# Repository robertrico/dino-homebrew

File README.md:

# DINO

**D**iscrete **I**ntegrated **N**ISC **O**perator — an 8-bit CPU built from
74-series logic. No microcontroller, no FPGA, no CPU chip: every register,
every bus, every gate is a chip you can put a probe on.

Schematics in KiCad, horizontal microcode in three EEPROMs, a ROM monitor
over a 16550 serial card, and SCELBAL BASIC running on it.

<table>
<tr>
<td width="50%"></td>
<td width="50%"></td>
</tr>
<tr>
<td><b>The prototype</b> (2026-09-10). Every module on breadboards, wired
by hand, running at 1.024 MHz.</td>
<td><b>Rev 1.0</b> (2026-10-29). The same netlist on one 4-layer board,
299 x 270 mm, eight card slots. Through fab review.</td>
</tr>
</table>

## Status, 2026-10-29

**The breadboard machine is complete.** It runs at 1.024 MHz off its own
crystal, executes from ROM and RAM, takes interrupts, and talks over serial.

- **174-instruction ISA.** `PROG_isa` passes 147 subtests; `PROG_isasoak`
  ran 50 consecutive passes (470,400 subtest executions) clean.
- **Stack, CALL/RET, execute-from-RAM.** All 32K of RAM (0x8000-0xFFFF)
  holds data and fetches instructions.
- **Memory-mapped I/O.** A 16K I/O window with eight 2K card slots: a DIP
  switch card and a PC16550D serial card at 9600 8N1.
- **ROM monitor.** `D`ump, `W`rite, `O`ut, `L`oad hex, `G`o (a CALL, so a
  RET comes back to the prompt).
- **Interrupts.** One vector, `0x9090` in RAM; the interrupt monitor takes
  serial input on the 16550's receive interrupt and breaks on Ctrl-C.
- **Add-with-carry.** `ADC`/`SBB`/`ACI`/`SBI` through one '157 on the ALU's
  carry-in.
- **SCELBAL BASIC** (the 1974 8008 BASIC), machine-translated into DINO
  assembly, runs out of ROM: `PRINT 2/3` gives ` 0.6666667`.

**Rev 1.0, the PCB.** Five boards ordered from PCBWay (2026-10-30).
4 layers (GND and +5V planes inside), KiCad DRC 0 unconnected / 0 errors,
schematic parity 0. Routed by Freerouting 2.5.0. Added for bring-up: a clock
select header (1.024 MHz, 512k, 256k, 128k, or a debounced single-step
button), a 16-signal logic analyzer header, 15 scope ground loops, and
unpopulated cap pads on the clock nets. Power is an ATX supply into the
24-pin header.

**Next:** bring Rev 1.0 up, move the serial card onto an edge card, then
CompactFlash and a floppy card. DINO will not get DMA; that goes to the
next machine.

---

## The machine

**8-bit data, 16-bit address.** Horizontal microcode, no pipeline. A
**24-bit control word** per T-state comes out of three AT28C64B EEPROMs
(`U9`, `U15`, `U23`) addressed by `{opcode, T-state}`. T0 is the fetch row
for every opcode; a '163 T-counter steps the rows until `END`.

The source, destination and misc fields are each a 3-bit '138 decode, with
bank-select bits for a second bank, so **two bus sources can never be on at
once**: mutual exclusion is the decoder, not the microcode's good behaviour.

**Memory map:**

```
0x0000-0x3FFF   ROM (U24, 28C256, 16K decoded)
0x4000-0x7FFF   I/O window, eight 2K card slots
                  0x4000 card 0  DIP switches
                  0x4800 card 1  PC16550D serial, 9600 8N1
0x8000-0xFFFF   RAM, 32K
```

**ALU:** two 74F382s, ripple carry. All four flags latch in a '273 and only
update when the ALU is the source.

**Commit discipline:** everything that changes state is clock-qualified and
commits while the clock is low — register loads through `NOR(~LOAD, CLK)`,
the RAM write through `NAND(WRITE_DIR, WR_GATE)`, PC load, clear and count
each gated on their own. Bus output enables are ungated, so a decode runt
lands while CLK is high and reaches nothing. The one exception was the fetch
row, where the instruction register is transparent during CLK low; the RAM
write is gated off in T-state 0 to close it. The machine is fully static, so
the clock can stop.

**HALT is `0xFF`**, so an erased EEPROM halts instead of running wild.

**Adding an instruction costs a three-ROM burn.** Image CRCs are pinned as
literals in `test_microcode_gen.py`, so a reburn is always deliberate.

---

## The part worth reading about

Building a CPU from discrete logic is a known exercise. The interesting
problem is different: **on a breadboard, with 80+ chips and a thousand
jumpers, how do you know the machine you built is the machine you drew?**

```
schematic  ──▶  netlist audit  ──▶  generated artifacts  ──▶  bench
 (KiCad)        (gate equations      (microcode, ROMs,        (coverage ROMs:
                 extracted, not       slot maps, landing       each one names
                 eyeballed)           lists, answer keys)      its expected byte)
```

The rule underneath it: **nothing is retyped.** Every table in this repo —
the microcode, the program ROMs, the breadboard slot maps, the wiring
landing lists, the card-edge pinout — is generated by a script with its own
host tests, most of them from the KiCad netlist. A hand-maintained table
drifts the moment someone moves a wire, and drift is invisible until it
costs you an evening.

Every test assertion is **netlist-verified before it is written**. Reading
a schematic and typing what you think a gate does is how you write a test
that agrees with your misunderstanding.

The answer key is `simulate()` in `progrom_gen.py`: it interprets the real
microcode rows and computes what the output LEDs should read for each
coverage image. Each image ends in `HALT` with one byte on the LEDs, and the
byte either matches or it names what broke.

### Rules that were paid for on the bench

Each of these exists because something went wrong first:

- **Rails first.** A random, probe-sensitive fault that doesn't care which
  program runs is not in the datapath. Measure ground and VCC on every board
  before building a logic model. One halt hunt (2026-09-01) was 460 mV of
  ground offset.
- **Mirror-witness.** A write-then-read through the same bus bank is
  permutation-blind — a flipped jumper bank cancels itself out. Every
  module needs at least one asymmetric path.
- **A witness that rewrites the same value sees nothing.** Every plant must
  differ from what the cell already held.
- **Rate is not data.** Halt rates moved from 7/8 to 1/22 with probes, a cap
  and warmth. Use a witness that cannot miss: a pulse trigger, a planted
  byte, a soak with a count.
- **A change that is logically identical and only faster is a timing
  change**, and the simulator is blind to it.
- **No blind counters.** A failing assertion must name the lying signal, or
  the test is just a rumour.

### Faults this method caught

| Fault | How it was found |
|---|---|
| `U18.1` (OE) on `MDR_OUT` instead of `~MDR_OUT` | enable polarity inverted; cascaded into four failing tests until bus-fight analysis fingered it |
| PORTF→MDR jumper bank reversed | invisible to every A/B/C round trip, caught only by the asymmetric OUT-register path |
| `MDR5`↔`MDR6` crossed | decoded from byte 0 arithmetic alone: `0xA5 → 0xC5` is exactly a bit-5/6 exchange |
| Bridge DIR/EN keyed on destination instead of source | schematic bug — ADD could never have committed. Found by netlist audit before the board existed |
| `A8`-`A11` address rotation on the microcode ROM | the address-order test named every rotated line |
| A RET fetched from RAM latching `0xFF` | a 14 ns `~WE` runt during the fetch row; caught on a pulse trigger, fixed by gating the write off in T-state 0 |
| The ALU latching half its next answer | its latch enable on raw CLK at the end of a stub sat at 1.0-1.2 V for 20 ns; now driven by a gate |

---

## Layout

```
dino_v0_0_2/     KiCad project: the mainboard schematics and the Rev 1.0 PCB
dino_bus/        card-edge connector symbol and socket footprint
dino_io/         card 0, the DIP switch card
dino_serial/     card 1, the 16550 serial card
asm/             program sources (.asm); asm/ram/ loads over serial
roms/            the burned images, CRCs and expected outputs (roms/README.md)
docs/notes/      generators, design notes, host tests
docs/captures/   scope, logic analyzer and PCB review captures
datasheets/      74-series and memory parts
```

| Script (`docs/notes/`) | Emits |
|---|---|
| `kicad_netlist.py` | `build_report()` — the netlist oracle everything else asks |
| `kicad_contracts.py` | per-sheet contracts, `--continuity` landing lists, `--since` change lists |
| `microcode_gen.py` | the three microcode images, CRCs, header |
| `progrom_gen.py` | program ROMs and the `simulate()` answer key |
| `isatest_gen.py` | the ISA self-test family (`isa`, `isasoak`, ...) |
| `roms_readme_gen.py` | `roms/README.md` — the inventory read at the burner |
| `layout_gen.py` | breadboard placement, slot maps, wiring guides |
| `bus_gen.py` | the card-edge pinout, symbol and footprint |
| `netsim_gen.py` | the twin: the Rev 1.0 netlist as gate-level Verilog (`netsim/`) |
| `netsim_suite.py` | every runnable image on the twin against the oracle (`make twin`) |

```bash
make test               # host tests
make expected           # every coverage image's expected output
make assemble-<name>    # asm/<name>.asm -> roms/PROG_<name>.bin
make load-<name>        # asm/ram/<name>.asm over serial into RAM
make monitor            # minicom on the serial card
```

Burning is done by hand on a TL866; the tools verify, they never program.

---

## Retired

**The ATmega2560 bring-up rig** brought the machine up one module at a
time, then one integration block at a time, shedding wires as each block
was proven. Retired 2026-08-24. `tests/dino_bringup/` stays for its ROM
burn targets.

**The FPGA twin** generated VHDL from an earlier netlist. It was perfect
logic, so it could not see the faults that mattered, which were build,
analog and glitch faults. Retired 2026-08-24 and deleted 2026-10-30. The
only twin now is `netsim/`: the Rev 1.0 netlist exactly as drawn, chip by
chip and pin by pin, simulated in Icarus with typical delays. `make twin`
runs every image that needs no card (43 of them, `isa` and `isasoak`
included) and all match the oracle. The breadboard had a fetch glitch that the T0 write
gate fixed; unmeasured on the PCB; the twin is logically identical, gate
included.

---

*Schematic PDF: [`dino_v0_0_2/dino_v0_0_2.pdf`](dino_v0_0_2/dino_v0_0_2.pdf)*

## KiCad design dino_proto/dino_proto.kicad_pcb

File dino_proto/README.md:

# dino_proto — the DINO prototype slot card

A perfboard with the bus edge and the slot decode every DINO card
repeats. Plug it into any of J1-J8 on the Rev 1.0 mainboard, pick the
slot with one shunt, bodge the card on the grid. Generated by
`docs/notes/proto_card_gen.py` from `bus_gen.BUS`; proved by
`docs/notes/test_proto_card.py`. Design and history: `.git/sdd/PROTO_CARD.md`.

    python3 docs/notes/proto_card_gen.py --write      # the project, unrouted
    python3 docs/notes/proto_card_gen.py --route 200  # Freerouting the band, DRC after

191.8 x 70 mm, 2-layer, all through-hole. The finger tab (65.8 mm) is
near the right end: the body runs 18 mm past the tab's right end (the
mainboard's edge is a future case wall; the cap is 20) and 108 mm to the
left, over the mainboard.

## What is on it

| Ref | Part | Does |
|-----|------|------|
| J1  | 2x25 fingers | the bus, pin n opposite pin n+25 (`PERIPHERAL_BUS.md` section 1) |
| J2  | 2x25 pin header | the edge repeated 1:1, pin n = edge pin n, numbered BY ROWS (1-25 front row, nearest the fingers; 26-50 back row) for a 50-way IDC ribbon to a breadboard. Silk: one label per column, "front/back", read as a picture of the column: the word at the top of the label is the top (back) hole, the word at the bottom the bottom (front) hole; "F/B" at pin 1; SPnn = spare, 3V3 = +3.3V |
| U1  | 74LS138 | slot decode: A0-A2 = M11-M13, E1 = `~{IO_SEL}`, E2 = GND, E3 = +5V, as the serial card's U101 |
| JP1 | 2x8 header | slot select, ONE shunt |
| U2  | 74LS32 | `~{CARD_RD}` = `~{CARD_SEL}` or `~{IO_RD_Q}`; `~{CARD_WR}` = `~{CARD_SEL}` or `~{IO_WR}`; two gates spare |
| J3  | 2x6 header | the decoded signals for the bodge |
| J4  | 1x4 header | the spare '32 gates |
| R1  | 4.7k | `~{CARD_SEL}` pull-up (no shunt = no window) |
| R2, R3 | 4.7k | park the spare gates (A high); leave one out to use its gate, see J4 |
| C1, C2 | 100 nF | U1, U2 decoupling |
| C3  | 10 uF | +5V bulk at the edge |

## JP1 — slot select

Top row `O0`..`O7` (the '138's outputs, left to right, silk 0-7); bottom
row all `~{CARD_SEL}`. One shunt in column n puts the card in slot n:

| slot | window        | slot | window        |
|------|---------------|------|---------------|
| 0    | 0x4000-0x47FF | 4    | 0x6000-0x67FF |
| 1    | 0x4800-0x4FFF | 5    | 0x6800-0x6FFF |
| 2    | 0x5000-0x57FF | 6    | 0x7000-0x77FF |
| 3    | 0x5800-0x5FFF | 7    | 0x7800-0x7FFF |

Two shunts short two '138 outputs together: never. Slot 0 is card zero
(the DIP switch), slot 1 the serial card, on the breadboard machine.

## J3 — the card's signals

| pin | signal          | pin | signal |
|-----|-----------------|-----|--------|
| 1   | `~{CARD_SEL}`   | 7   | `O3`   |
| 2   | `~{CARD_RD}`    | 8   | `O4`   |
| 3   | `~{CARD_WR}`    | 9   | `O5`   |
| 4   | `O0`            | 10  | `O6`   |
| 5   | `O1`            | 11  | `O7`   |
| 6   | `O2`            | 12  | GND    |

`O0`-`O7` are the raw decoder outputs, for a bodge that wants a second
window. The rule for every card (PHASE_G): drive W only while
`~{CARD_RD}` is low, take data on `~{CARD_WR}`; nothing else goes back
on the bus (CARD-2).

## J4 — the spare '32 gates

| pin | signal | gate |
|-----|--------|------|
| 1   | 3B     | gate 3 input; 3A pulled up by R2 |
| 2   | 3Y     | gate 3 output |
| 3   | 4B     | gate 4 input; 4A pulled up by R3 |
| 4   | 4Y     | gate 4 output |

With A pulled high an OR gate's output is high whatever B does. To use
a spare gate as a 2-input OR, leave its pull-up out (R2 for gate 3, R3
for gate 4) and wire A at the empty resistor's pad: the one on the U2
side is U2 pin 9 (3A) / pin 12 (4A). With the pull-up fitted the gate
is parked.

## The grid

0.1 in plated holes, drill 1.0 mm, pad 1.8 mm, both sides, every hole
on its own. Rows top to bottom: +12, -12, 3V3 (square holes, one row
each), then +5V / A-E / GND, +5V / F-J / GND, +5V / K-M. A rail row is a
row of SQUARE holes joined by a masked trace (GND 1.5 mm, +5V 1.2 mm,
bias 0.6 mm, both layers); the round holes beside it are free. A 0.3 in
DIP sits on a band's rows 1 and 4 with VCC and GND one row away.
Columns 1-71 numbered every fifth on the top edge, rows lettered on the
right. No track of the card's own copper runs through the grid (rule
areas, DRC-checked).

The band's own +5V and GND rails are hole-less traces just above the
chips, fed from the grid's rows down the left margin. The six J2-to-band
signals (M11-M13, `~{IO_SEL}`, `~{IO_RD_Q}`, `~{IO_WR}`) run as lanes
between the grid and the band.

## Rails on the edge

+5V, GND, +12V, -12V, +3.3V are what the ATX unit delivers (POWER.md
section 8). -12V is 50-100 mA for the whole machine. This card draws
nothing from +12V/-12V/+3.3V itself; a bodge that does declares it.

## Fab

PCBWay 2-layer, 1.6 mm, gold fingers with a bevel. Open before the
first order: the Sullins EBC25DCWN slot opening against the 65.8 mm tab
(no catalog on disk; `PERIPHERAL_BUS.md` OPEN 2).

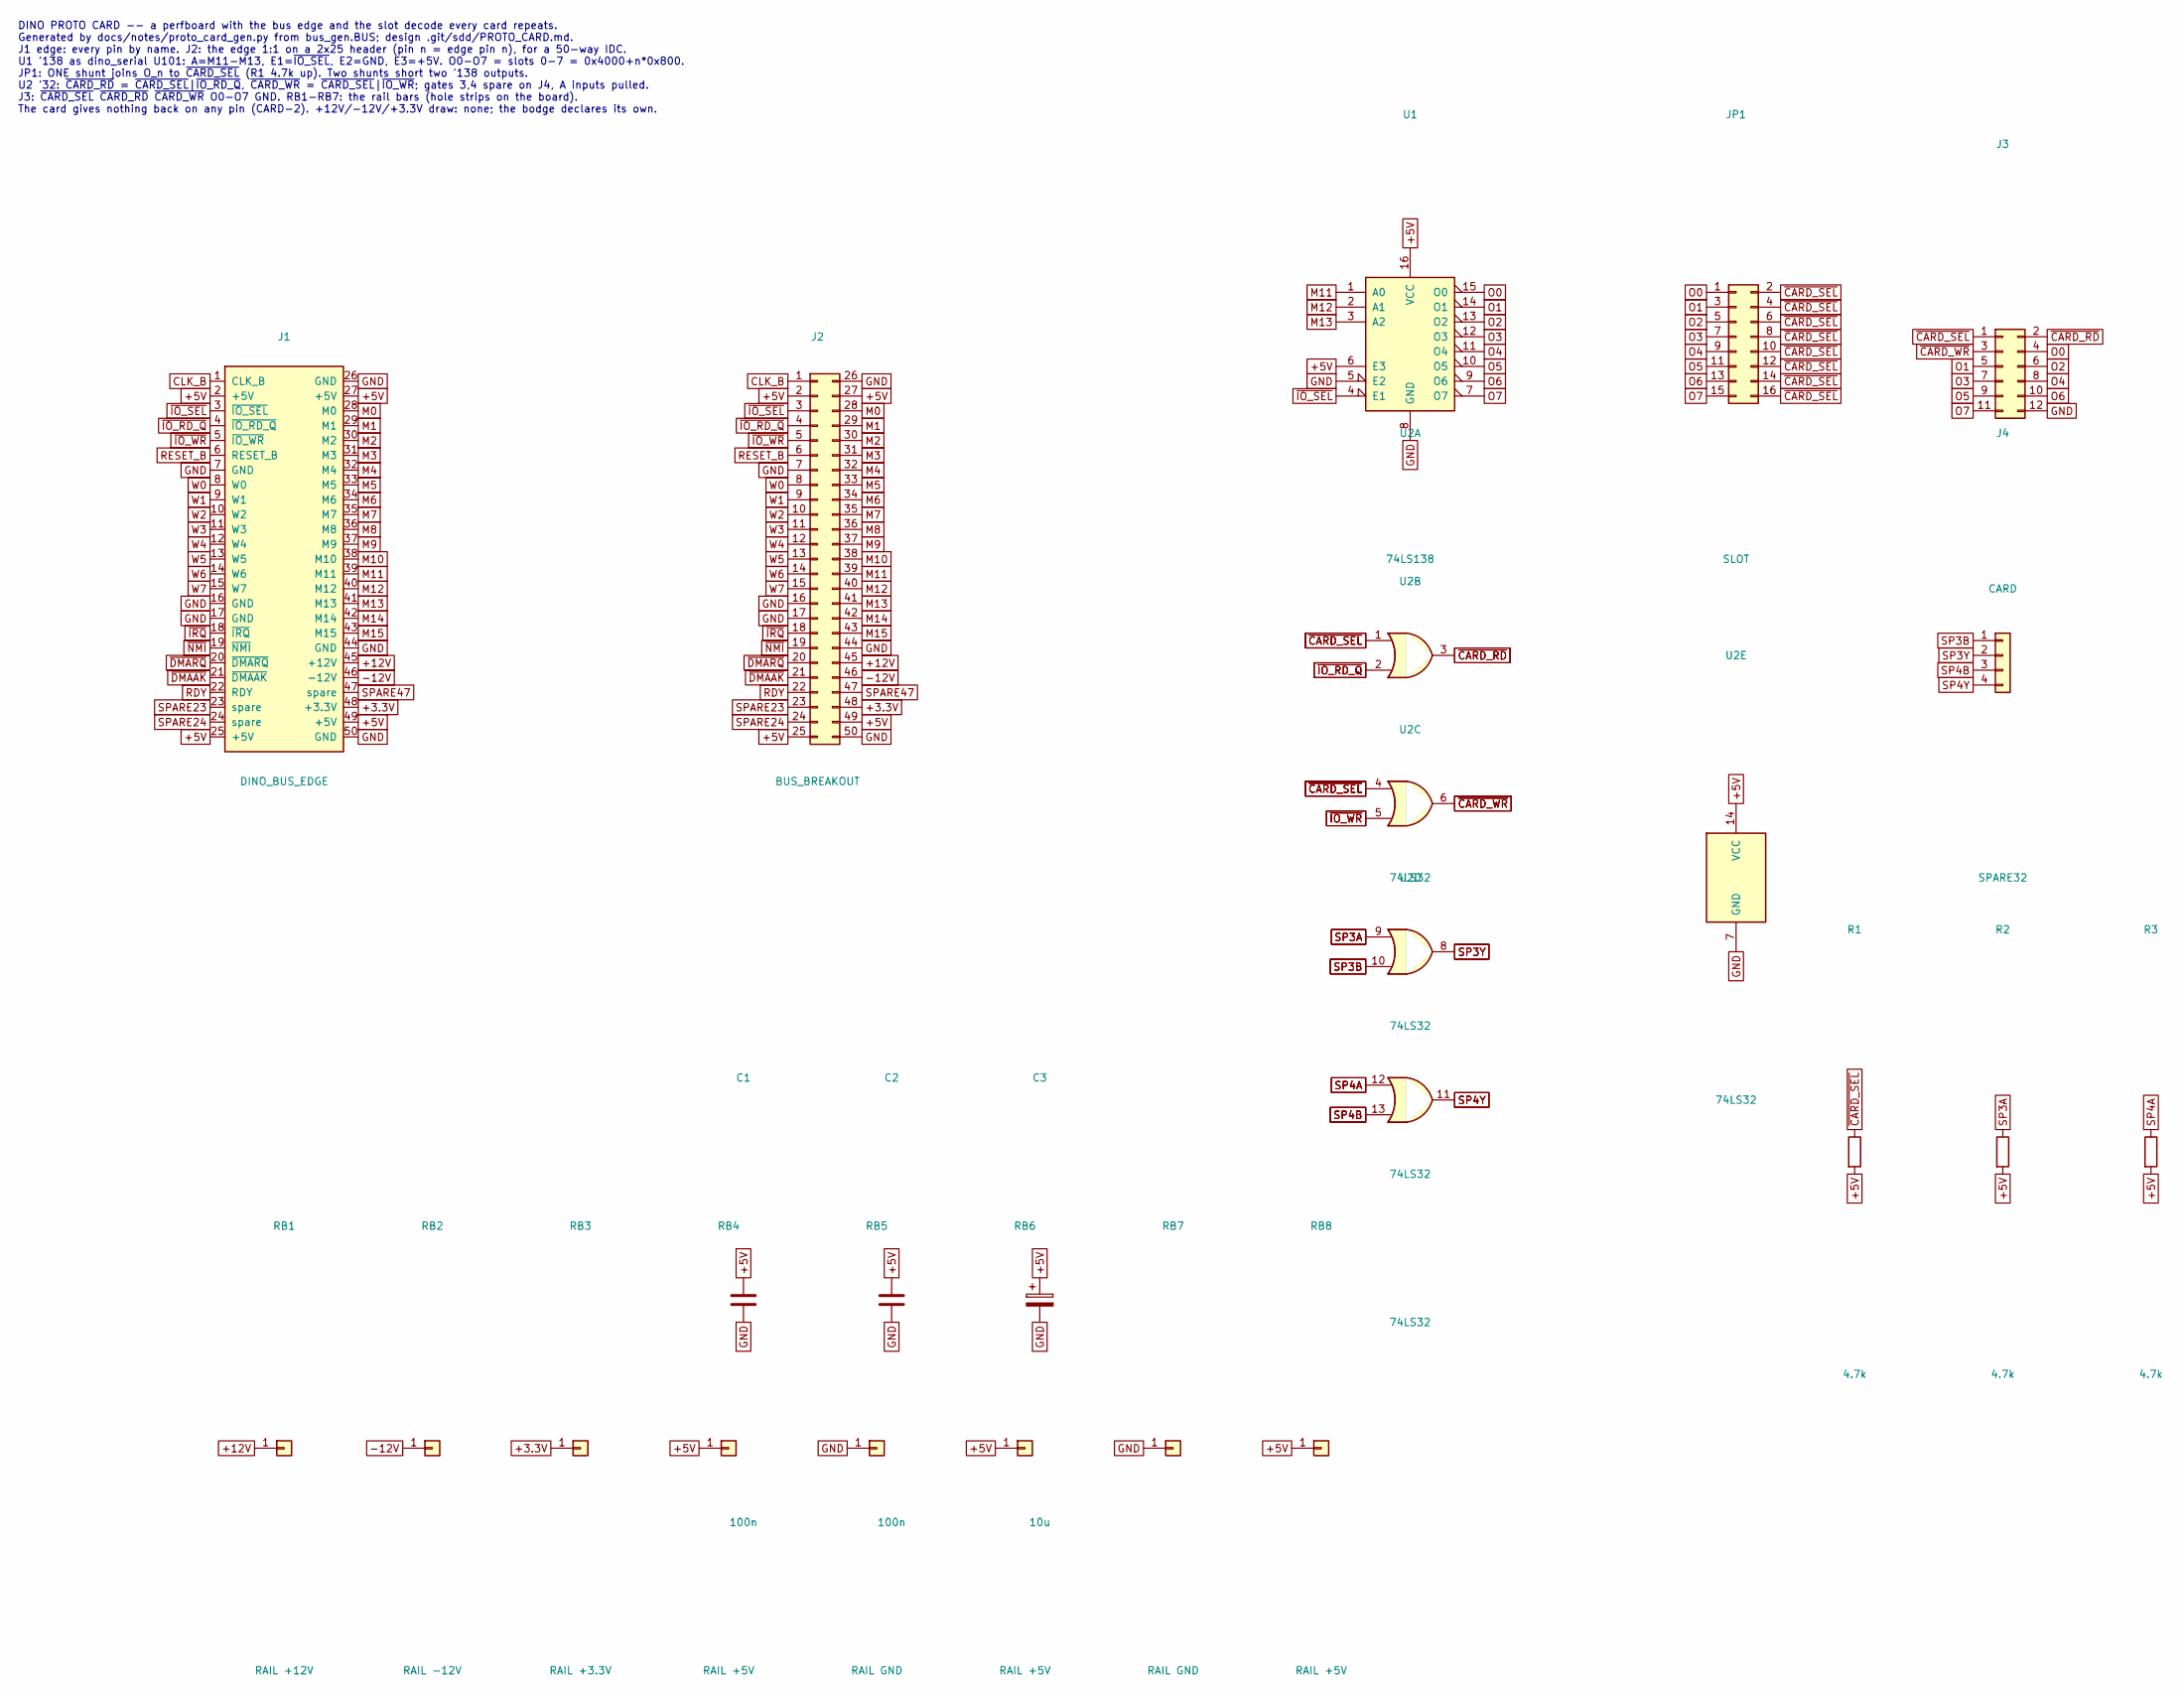
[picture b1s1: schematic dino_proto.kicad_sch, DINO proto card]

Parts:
C1, C2: 100n; C_Disc_D5.0mm_W2.5mm_P5.00mm
C3: 10u; CP_Radial_D5.0mm_P2.50mm
J1: DINO_BUS_EDGE; EdgeFingers_2x25_P2.54mm
J2: BUS_BREAKOUT; PinHeader_2x25_Rows_P2.54mm
J3: CARD; PinHeader_2x06_P2.54mm_Vertical
J4: SPARE32; PinHeader_1x04_P2.54mm_Vertical
JP1: SLOT; PinHeader_2x08_P2.54mm_Vertical
R1, R2, R3: 4.7k; R_Axial_DIN0207_L6.3mm_D2.5mm_P7.62mm_Horizontal
RB1: RAIL +12V; RailHoles_1x71_P2.54mm
RB2: RAIL -12V; RailHoles_1x71_P2.54mm
RB3: RAIL +3.3V; RailHoles_1x71_P2.54mm
RB4, RB6, RB8: RAIL +5V; RailHoles_1x71_P2.54mm
RB5, RB7: RAIL GND; RailHoles_1x71_P2.54mm
U1: 74LS138; DIP-16_W7.62mm_Socket
U2: 74LS32; DIP-14_W7.62mm_Socket

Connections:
+3.3V: J1.48 (+3.3V), J2.48, RB3.1
+5V: C1.1, C2.1, C3.1, J1.2 (+5V), J1.25 (+5V), J1.27 (+5V), J1.49 (+5V), J2.2, J2.25, J2.27, J2.49, R1.2, R2.2, R3.2, RB4.1, RB6.1, RB8.1, U1.6 (E3), U1.16 (VCC), U2.14 (VCC)
+12V: J1.45 (+12V), J2.45, RB1.1
-12V: J1.46 (-12V), J2.46, RB2.1
CLK_B: J1.1 (CLK_B), J2.1
GND: C1.2, C2.2, C3.2, J1.7 (GND), J1.16 (GND), J1.17 (GND), J1.26 (GND), J1.44 (GND), J1.50 (GND), J2.7, J2.16, J2.17, J2.26, J2.44, J2.50, J3.12, RB5.1, RB7.1, U1.5 (E2), U1.8 (GND), U2.7 (GND)
M0: J1.28 (M0), J2.28
M1: J1.29 (M1), J2.29
M2: J1.30 (M2), J2.30
M3: J1.31 (M3), J2.31
M4: J1.32 (M4), J2.32
M5: J1.33 (M5), J2.33
M6: J1.34 (M6), J2.34
M7: J1.35 (M7), J2.35
M8: J1.36 (M8), J2.36
M9: J1.37 (M9), J2.37
M10: J1.38 (M10), J2.38
M11: J1.39 (M11), J2.39, U1.1 (A0)
M12: J1.40 (M12), J2.40, U1.2 (A1)
M13: J1.41 (M13), J2.41, U1.3 (A2)
M14: J1.42 (M14), J2.42
M15: J1.43 (M15), J2.43
O0: J3.4, JP1.1, U1.15 (O0)
O1: J3.5, JP1.3, U1.14 (O1)
O2: J3.6, JP1.5, U1.13 (O2)
O3: J3.7, JP1.7, U1.12 (O3)
O4: J3.8, JP1.9, U1.11 (O4)
O5: J3.9, JP1.11, U1.10 (O5)
O6: J3.10, JP1.13, U1.9 (O6)
O7: J3.11, JP1.15, U1.7 (O7)
RDY: J1.22 (RDY), J2.22
RESET_B: J1.6 (RESET_B), J2.6
SP3A: R2.1, U2.9
SP3B: J4.1, U2.10
SP3Y: J4.2, U2.8
SP4A: R3.1, U2.12
SP4B: J4.3, U2.13
SP4Y: J4.4, U2.11
SPARE23: J1.23 (spare), J2.23
SPARE24: J1.24 (spare), J2.24
SPARE47: J1.47 (spare), J2.47
W0: J1.8 (W0), J2.8
W1: J1.9 (W1), J2.9
W2: J1.10 (W2), J2.10
W3: J1.11 (W3), J2.11
W4: J1.12 (W4), J2.12
W5: J1.13 (W5), J2.13
W6: J1.14 (W6), J2.14
W7: J1.15 (W7), J2.15
~CARD_RD: J3.2, U2.3
~CARD_SEL: J3.1, JP1.2, JP1.4, JP1.6, JP1.8, JP1.10, JP1.12, JP1.14, JP1.16, R1.1, U2.1, U2.4
~CARD_WR: J3.3, U2.6
~DMAAK: J1.21 (~DMAAK), J2.21
~DMARQ: J1.20 (~DMARQ), J2.20
~IO_RD_Q: J1.4 (~IO_RD_Q), J2.4, U2.2
~IO_SEL: J1.3 (~IO_SEL), J2.3, U1.4 (E1)
~IO_WR: J1.5 (~IO_WR), J2.5, U2.5
~IRQ: J1.18 (~IRQ), J2.18
~NMI: J1.19 (~NMI), J2.19

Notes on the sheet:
DINO PROTO CARD -- a perfboard with the bus edge and the slot decode every card repeats. Generated by docs/notes/proto_card_gen.py from bus_gen.BUS; design .git/sdd/PROTO_CARD.md. J1 edge: every pin by name. J2: the edge 1:1 on a 2x25 header (pin n = edge pin n), for a 50-way IDC. U1 '138 as dino_s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

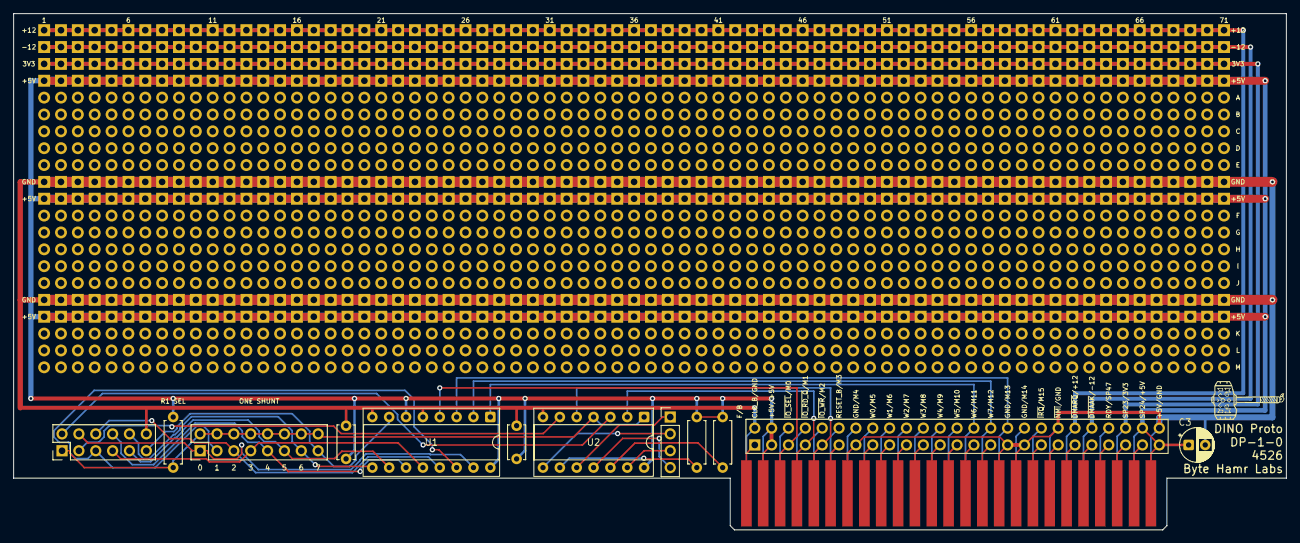
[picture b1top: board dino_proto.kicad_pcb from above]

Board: 2 copper layers, 191.8 x 77.8 mm, 23 parts (0 on the bottom side), 59 nets.

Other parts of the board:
G1: ProtoGrid_923_P2.54mm
LOGO1: hamr_logo_xs

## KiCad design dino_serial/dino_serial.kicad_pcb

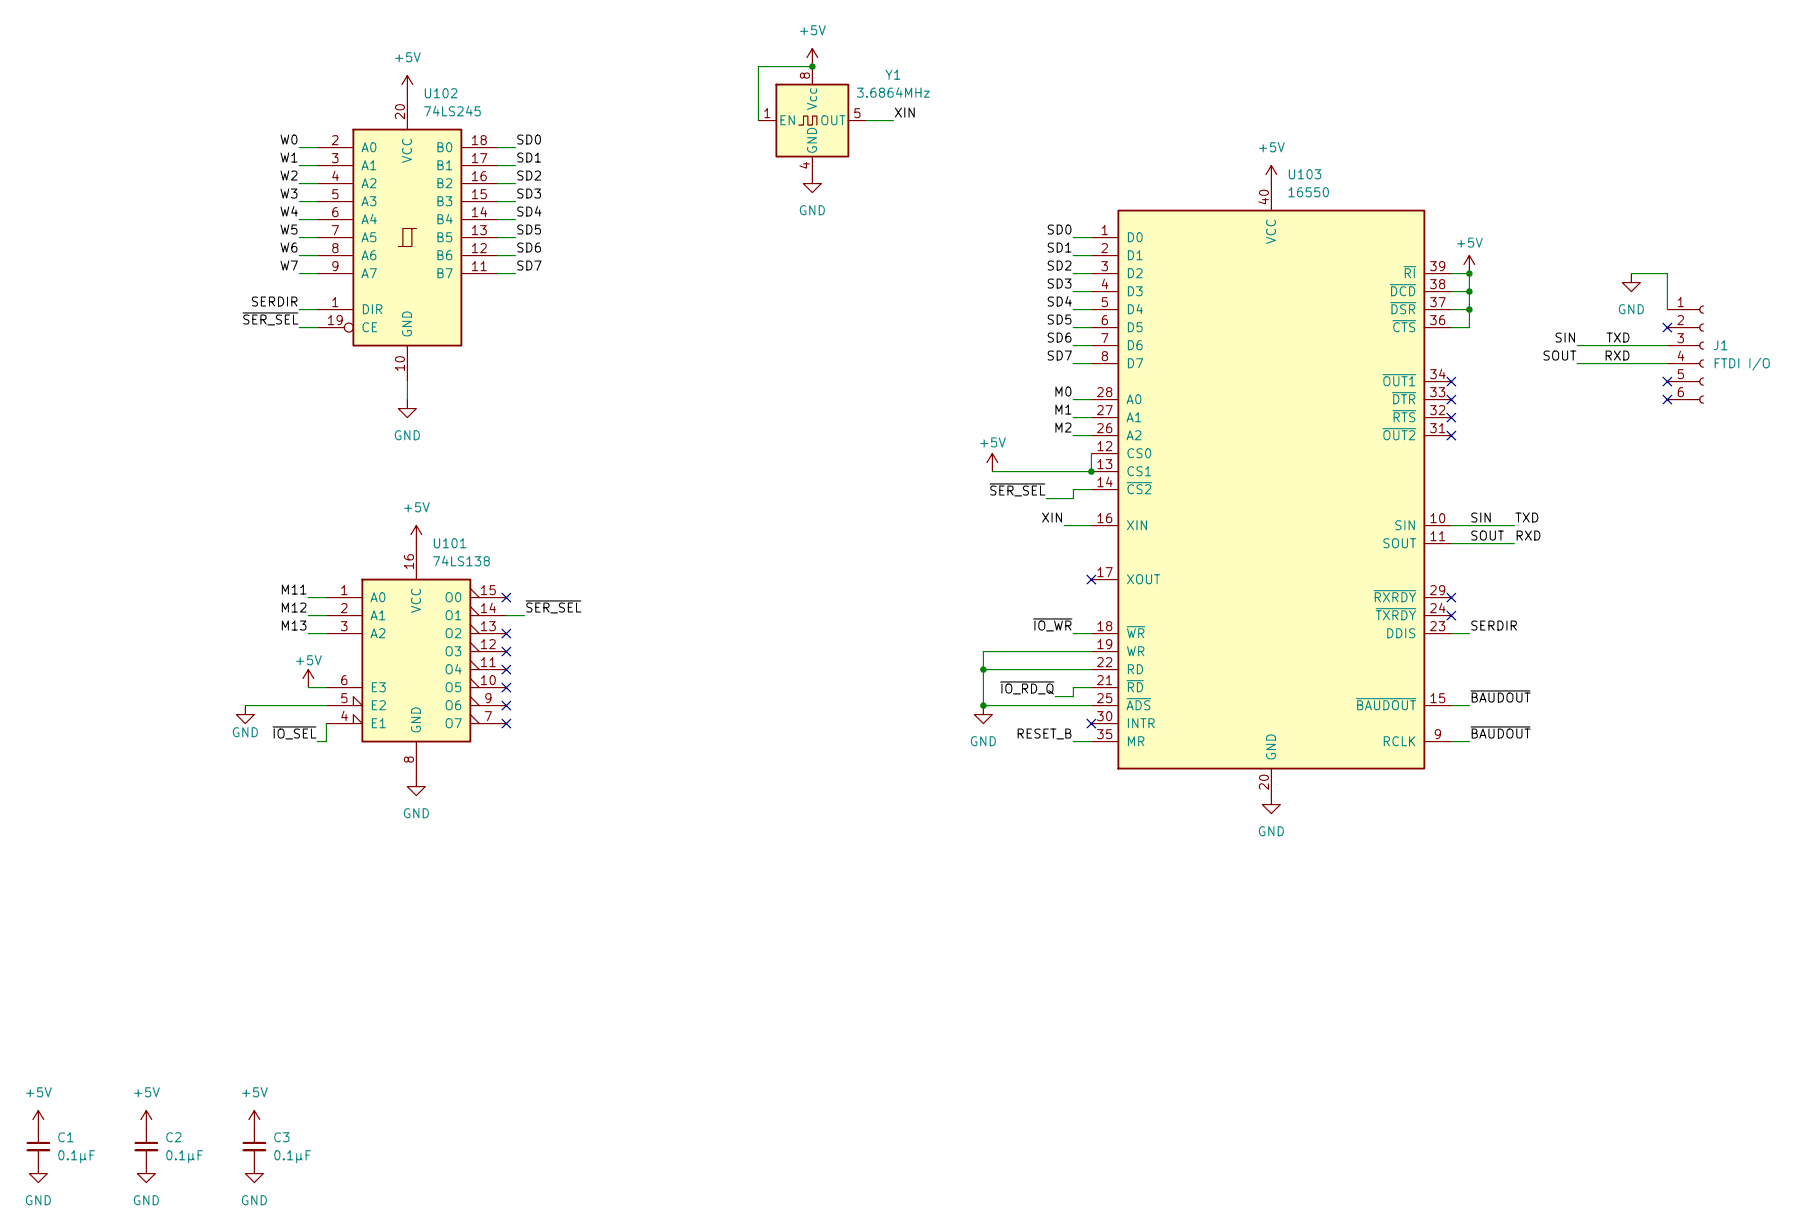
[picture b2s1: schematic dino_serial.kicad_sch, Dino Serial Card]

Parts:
C1, C2, C3: 0.1µF; C_Disc_D10.0mm_W2.5mm_P5.00mm
J1: FTDI I/O; PinSocket_1x06_P2.54mm_Vertical
U101: 74LS138; DIP-16_W7.62mm
U102: 74LS245; DIP-20_W7.62mm
U103: 16550; DIP-40_W15.24mm
Y1: 3.6864MHz; Oscillator_DIP-8

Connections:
+5V: C1.1, C2.1, C3.1, U101.6 (E3), U101.16 (VCC), U102.20 (VCC), U103.12 (CS0), U103.13 (CS1), U103.36 (~CTS), U103.37 (~DSR), U103.38 (~DCD), U103.39 (~RI), U103.40 (VCC), Y1.1 (EN), Y1.8 (Vcc)
/M0: U103.28 (A0)
/M1: U103.27 (A1)
/M2: U103.26 (A2)
/M11: U101.1 (A0)
/M12: U101.2 (A1)
/M13: U101.3 (A2)
/RESET_B: U103.35 (MR)
/RXD: J1.4, U103.11 (SOUT)
/SD0: U102.18 (B0), U103.1 (D0)
/SD1: U102.17 (B1), U103.2 (D1)
/SD2: U102.16 (B2), U103.3 (D2)
/SD3: U102.15 (B3), U103.4 (D3)
/SD4: U102.14 (B4), U103.5 (D4)
/SD5: U102.13 (B5), U103.6 (D5)
/SD6: U102.12 (B6), U103.7 (D6)
/SD7: U102.11 (B7), U103.8 (D7)
/SERDIR: U102.1 (DIR), U103.23 (DDIS)
/SIN: J1.3, U103.10 (SIN)
/W0: U102.2 (A0)
/W1: U102.3 (A1)
/W2: U102.4 (A2)
/W3: U102.5 (A3)
/W4: U102.6 (A4)
/W5: U102.7 (A5)
/W6: U102.8 (A6)
/W7: U102.9 (A7)
/XIN: U103.16 (XIN), Y1.5 (OUT)
/~BAUDOUT: U103.9 (RCLK), U103.15 (~BAUDOUT)
/~IO_RD_Q: U103.21 (~RD)
/~IO_SEL: U101.4 (E1)
/~IO_WR: U103.18 (~WR)
/~SER_SEL: U101.14 (O1), U102.19 (CE), U103.14 (~CS2)
GND: C1.2, C2.2, C3.2, J1.1, U101.5 (E2), U101.8 (GND), U102.10 (GND), U103.19 (WR), U103.20 (GND), U103.22 (RD), U103.25 (~ADS), Y1.4 (GND)

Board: 2 copper layers, 8 parts (0 on the bottom side), 16 nets, no tracks yet.

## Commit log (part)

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2025-06-15 Adds documentation and removes obsolete lock file
    Introduces new PDF and DOCX documentation files to the 'dino' directory, enhancing reference materials.
    Removes an outdated KiCad schematic lock file to ensure file system cleanliness.
2025-06-15 Adds initial dinosaur version PDFs
    Introduces Dino_v0_0_1.pdf and Dino_v0_1.pdf to the project
    to provide baseline documentation for the dinosaur versions.
2025-06-16 Removes backup files and updates .gitignore
    Deletes several backup ZIP files from the repository.
    Adds a new pattern to .gitignore to prevent future
    backup files from being tracked.
    Enhances project cleanliness by avoiding unnecessary
    backup files in version control.
2025-06-17 Organizes datasheets and updates schematics
    Renames PDF resources into a dedicated 'datasheets' folder
    for better organization and clarity. Removes outdated PDFs
    to improve project maintainability. Enhances schematic by
    adding resistor symbol and adjusting LED positions for
    optimized layout. Moves DOCX files to 'docs' directory, keeping
    versions clear and manageable.
2025-06-18 Motor Control Board
    And PDF
2025-06-22 Adds initial version of Dino PDF
    Introduces version 0.0.1 of the Dino schematic.
2025-06-23 Removes redundant GND label and updates UUIDs
    Eliminates duplicate GND label entry to avoid confusion.
    Updates UUIDs across multiple pins for consistency and accuracy.
    Renames and reorganizes documentation files to improve clarity.
    Removes outdated temporary document files.
    Improves document organization and maintains schematic integrity.
2025-06-23 Updates schematic connections and increments revision
    Adjusts various schematic wire and bus connections for improved accuracy and clarity, removes obsolete bus entries, and adds new GND label and connection points. Increments schematic revision to v1.0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
    Enhances maintainability and correctness of the design.
2025-06-23 Updates DINO Schematic PDF
2025-06-24 Updates documentation and restructures project ideas
    Adds high-level project plans for Intel 8008 LED Blinker and Motorola 6808 Digital Thermometer, detailing goals, phases, and extensions.
    Introduces improved project categorization by renaming and relocating project list.
2025-06-30 Adds datasheet, documentation, and test files
    Introduces relevant hardware datasheets and new documentation files to support project development. Includes a new test case for further validation and several temp files likely associated with activ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
2025-06-30 Updates schematic with corrections
    - Corrects ~CE on 74LS645
    - Fixes MCM60256AP DQ6 Pin Number
    - Removes "Net Label" for +5V and adds correct text label
    - Attaches both GND and VCC to bus proper
2025-07-02 Updates schematic for DIP switch change
    Replaces 7x DIP switch with 8x DIP switch in schematic.
    Modifies connection points and properties accordingly.
    Adjusts bus and wire entries for compatibility.
2025-07-03 Update schematic revision and remove temporary files
    Increments revision number in schematic files to v1.0.3 and updates
    the date to reflect recent changes. Removes auto-saved and lock files
    to clean up the directory.
    Ensures only essential files are retained following design updates.
2025-07-04 Add link to project repository in scratch file
    Created a new scratch file and added a link to the minipro EEPROM burner project repository.
2025-07-08 Adds new documentation files
    Includes a new PDF for the Dino project documentation and
    a DOCX detailing a Motorola Motor Control Board concept.
    These additions enhance project reference materials.
2025-07-08 Removes obsolete draft documents
    Deletes outdated draft documents from the repository to reduce
    clutter and improve document management.
    No longer in use as they have been superseded by updated versions.
2025-07-19 Adds datasheets for various components
    Introduces new PDF datasheets for electronic components, facilitating easier access to specifications and technical data for development and reference purposes.
2025-07-19 Migrates project to version 0.0.2 with Ring Counter addition
    Renames existing project files from version 0.0.1 to 0.0.2 to reflect updates.
    Adds a new sub-circuit named "RingCounter" to the schematic, improving functionality.
    Updates date and revision information in title blocks to keep documentation current.
    Integrates new wires, junctions, and labels into existing schematics to accommodate the RingCounter.
2025-07-20 Adds new documentation screenshot
    Introduces an updated screenshot to enhance the documentation's visual references and clarity for users.
2025-07-20 Control Unit Images
2025-07-21 Reorganizes and updates dino project files
    Renames and relocates dino files for improved project
    structure, moving PDFs to a dedicated docs directory.
    Addresses organizational concerns for better maintainability.
2025-07-21 Removes draft and final documentation files
    Deletes outdated PDF and DOCX files from the project repository,
    streamlining documentation by removing obsolete or redundant content.
2025-07-26 Adds ring counter 16-state test case
    Introduces a new test to verify 16-state ring counter functionality,
    enabling more comprehensive validation of state transitions and behavior.
2025-07-31 Adds initial DSL test file for version 0.0.2
    Introduces a new binary DSL test file to support validation and regression testing for the 0.0.2 release. Enhances coverage of supported features.
2025-08-01 Adds new screenshot image for documentation
    Introduces a new screenshot to enhance visual guidance in the documentation.
2025-08-08 Schematics WIP
2025-08-09 Changed Pages to 8.5x11
2025-08-10 KiCAD Updates
2025-08-12 Add EEPROM initialization and verification code - Initialize two EEPROM arrays with zeros - Write specific values to addresses in the EEPROM arrays - Add a program to verify and print values at key a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
2025-08-16 KiCAD Updates
    - Updating Memory Module
2025-08-17 Adds RAM test program for AT28C64 EEPROM
    Introduces a write-read verification program to test RAM using
    a series of predefined patterns for EEPROM devices. Ensures data
    integrity through DMM verification, highlighting the sequence
    of writing and reading while preserving write-enable edges.
    Includes EEPROM image creation for external use.
2025-08-19 Memory Register Module Update
    With some previous learnings on the 74LS121, the MDR Module has been re-sketched to better trigger the '121 and create an intra phase latch. This should allow the data bus to stabilize before the the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
2025-08-22 Plot Update: DINO
2025-08-24 Refactors Arduino and Pico projects for flexible testing
    - Replaces hardcoded Arduino blink example with a more modular test framework supporting multiple hardware tests via compile-time flags
    - Adds comprehensive guide and updated CMake configuration for AVR development and flexible test selection
    - Implements 74LS373 latch self-test for Arduino with robust data bus validation
    - Updates Pico CMake and blink example for USB stdio and onboard LED, improving debug and portability
    - Adjusts environment and build scripts for updated hardware ports
    Enables more scalable hardware validation workflows and improved maintainability.
2025-08-24 Changes schematic paper size and handles PDF file
    Updates ALU schematic paper size from A4 to USLetter to align
    with standard printing requirements. Adds a new PDF plot and
    handles its removal, possibly for version management or
    regeneration purposes.
2025-08-24 Removes unused hex file and updates bus initialization
    Deletes an obsolete test hex file to clean up test resources.
    Replaces a function call with explicit pin configuration in the bus
    initialization function for improved clarity and control.
2025-08-24 Schematic Updates
    - Flipped 74LS245 Bus Transceivers on Register modules
2025-08-24 Adds new test DSL file for IR scenarios
    Introduces a new binary DSL test file to support testing
    of intermediate representation cases in the current version.
2025-08-24 Refactors register test to use unified control word
    Replaces individual control signal manipulation with a single 3-bit control word to simplify logic and improve hardware timing consistency. Updates documentation, pin definitions, and the test sequen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
    - Removes manual latch pulse triggers in favor of logic-driven pulses
    - Revises bus access and state transitions for more robust operation
    - Clarifies comments to better reflect hardware state and flow
2025-08-27 Updates PDF in plots directory
    Removes previous PDF file from plots directory and adds
    a new version of the PDF, improving documentation clarity
    or reflecting updated information.
2025-08-27 Adds script for building and flashing Arduino tests
    Introduces a shell script to streamline the build process for
    Arduino test modules with support for different test types and
    optional flashing to Arduino. Enhances ease of testing and deployment.
2025-08-27 Adds timing test DSL case and oscilloscope captures
    Introduces a new DSL test case for register timing issues.
    Includes a set of oscilloscope screenshots to provide visual
    evidence and aid in debugging timing-related behaviors.
2025-08-30 KiCAD Update
    - Fixed Pins to match hardware
    - Fixed DIR on '245 Pair for Reg A+B
2025-08-30 Add configurable clock generator test for AVR modules
    - Introduces a standalone clock generator test supporting selectable frequency via build options
    - Updates build script and CMake to support clock frequency parameter
    - Adds new source file for clock generation using Timer1 with output on specified pins
    - Enhances build script usage instructions and argument parsing to accommodate the new feature
    Enables testing of various clock signals and eases automated clock module verification.
2025-08-30 Successfully validate register module with 74LS373/245/121
    Added comprehensive test for register module that validates:
    - Data latching via 74LS121-generated pulse
    - Data retention during bus activity
    - Bidirectional bus operation through 74LS245
    - Proper isolation when control signals are idle
    Test patterns adjusted to work around Arduino D13 LED load limitation.
2025-09-01 Documents project retirement and technical postmortem
    Adds a comprehensive summary detailing the discontinuation
    of the DINO 8-bit CPU project, outlining design milestones,
    completed modules, encountered signal integrity issues, and
    root causes for failure at target clock speed. Provides an
    in-depth retrospective and recommendations for future
    hardware implementations.
2025-09-02 Add oscilloscope capture images for dino and earth_rover tests.
2025-10-14 Separate Registers from Trigger Logic
2025-10-15 Adds ATMega2560 test rig for DINO
    - Adds test code to control GPIO and test pulse logic
    - Enables streamlined development and testing workflow for AVR-based projects
